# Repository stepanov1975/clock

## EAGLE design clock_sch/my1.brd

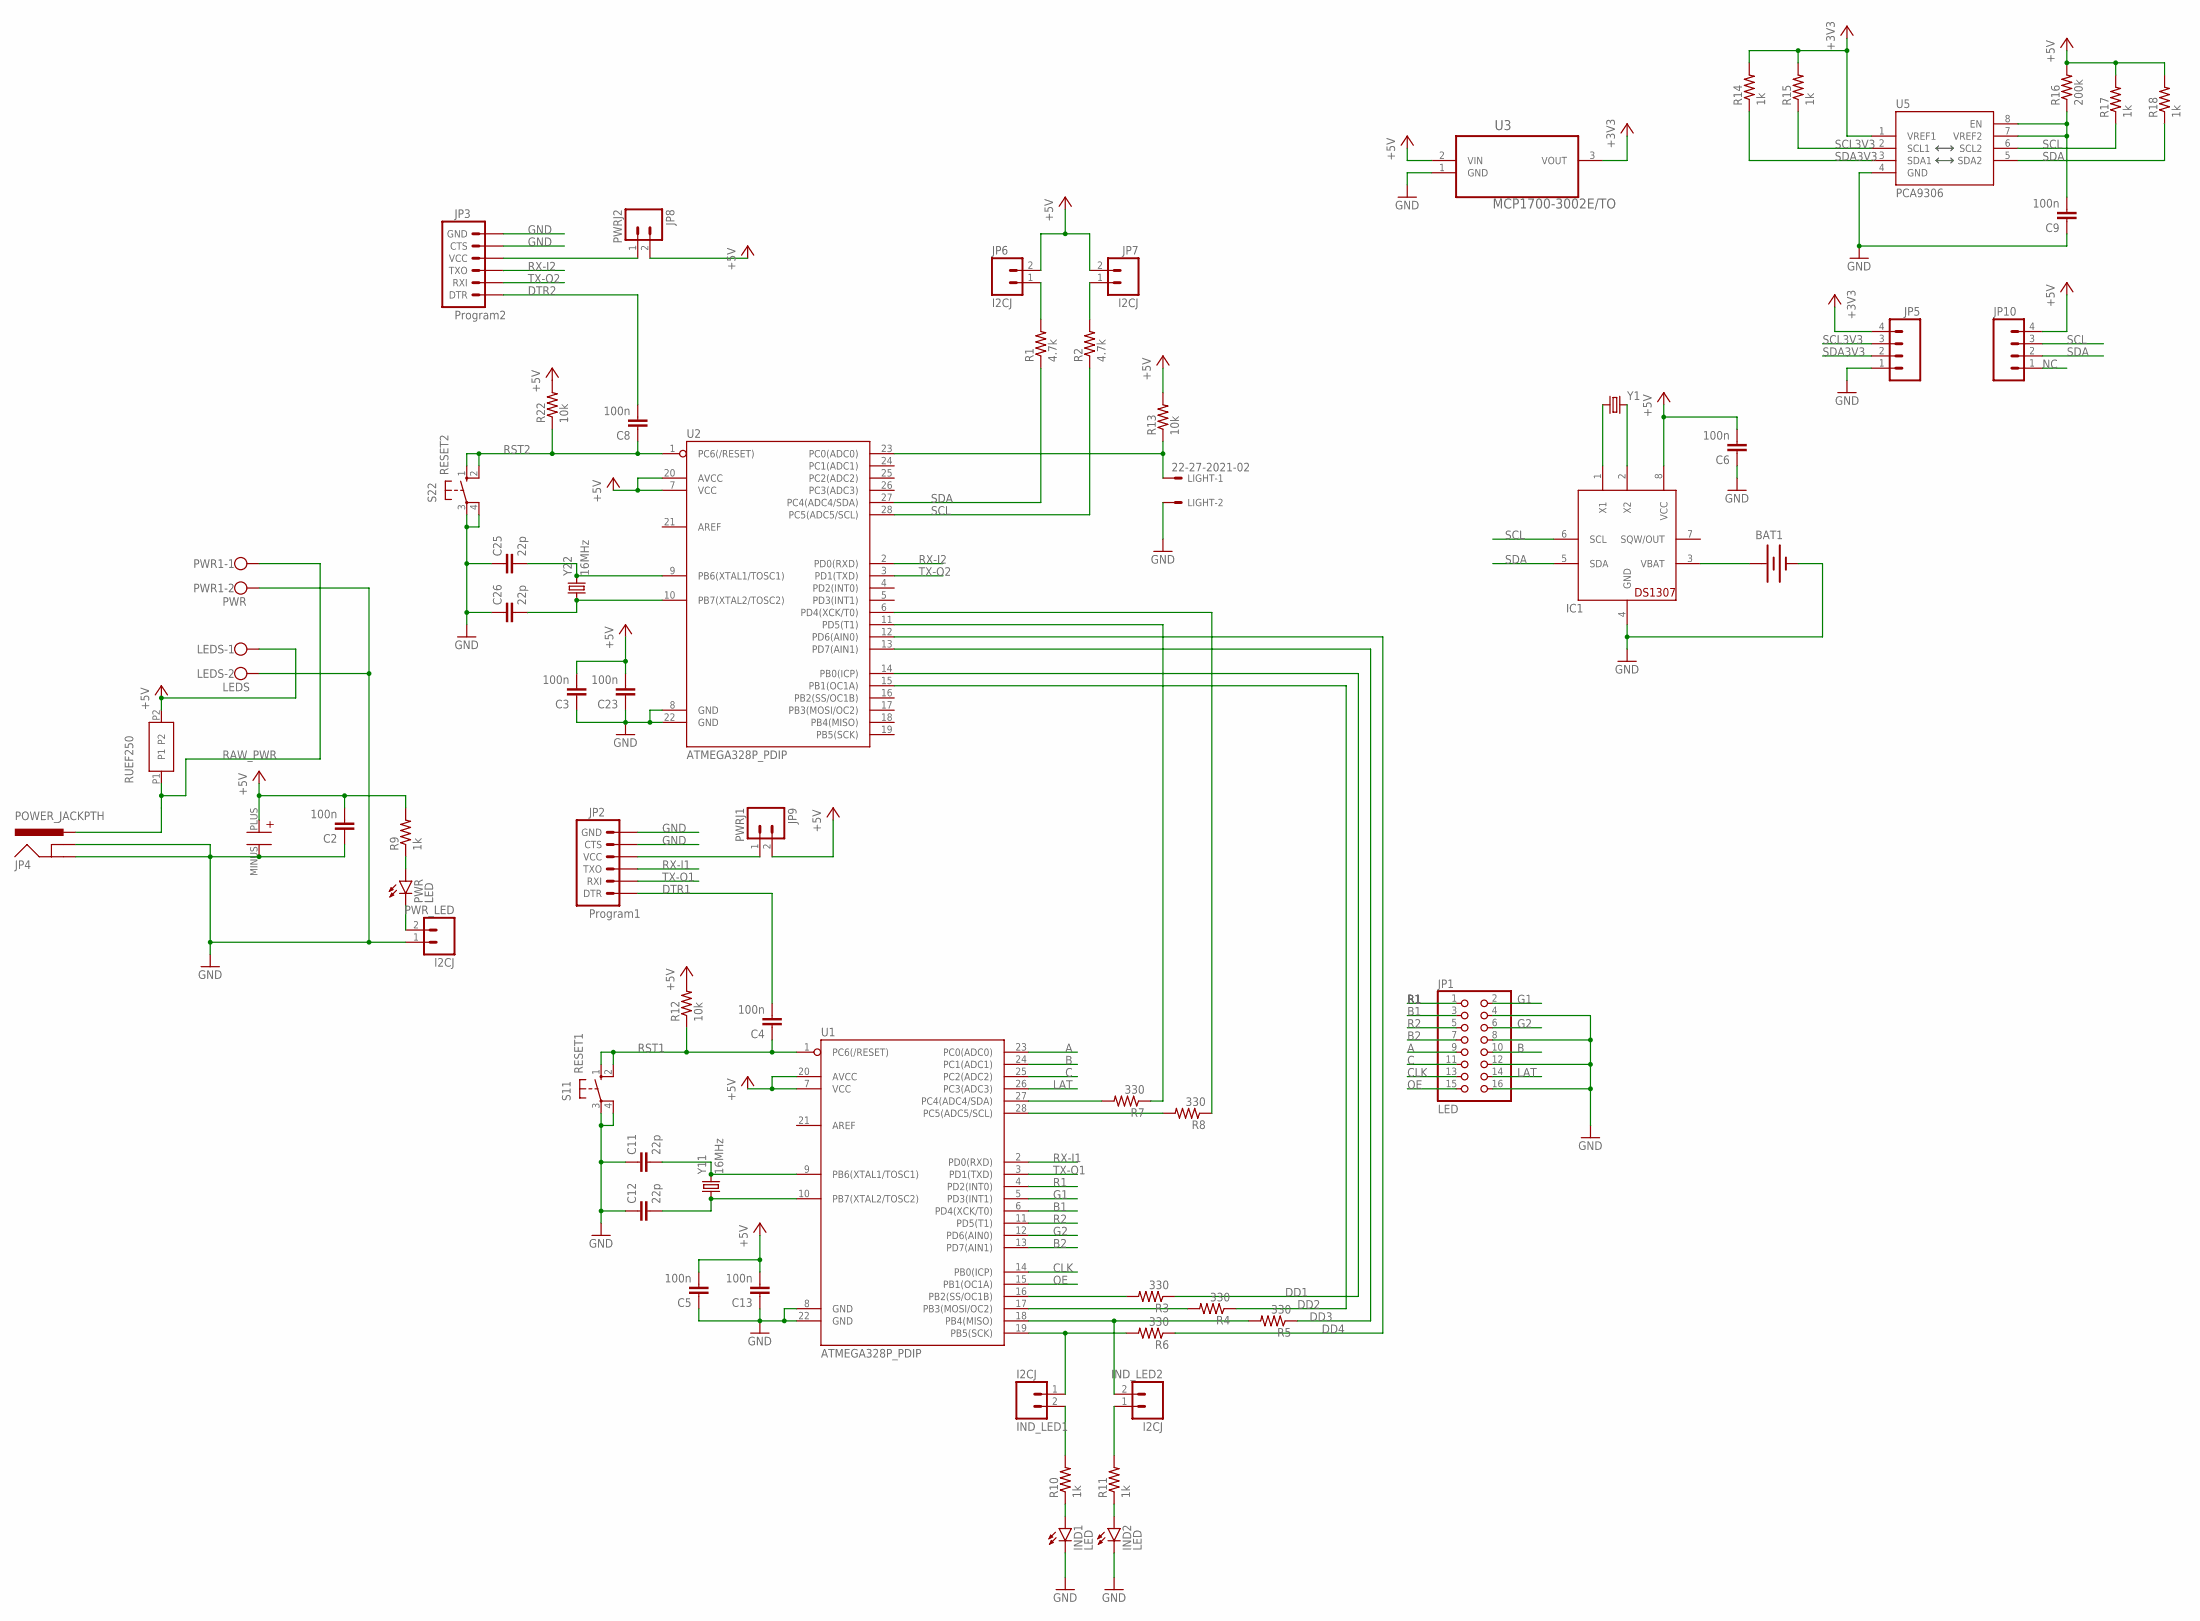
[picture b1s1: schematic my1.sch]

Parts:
BAT1: BATTERY12MM; BATTCON_12MM
C1: EEU-FR1C471B
C2, C3, C4, C5, C6, C8, C9, C13, C23: 100n; C025-024X044
C11, C12, C25, C26: 22p; C025-024X044
IC1: DS1307; DIL08
IND1, IND2: LED; LED5MM
IND_LED1, IND_LED2: I2CJ; 1X02
JP1: LED; 2X08
JP2: Program1; 1X06
JP3: Program2; 1X06
JP4: POWER_JACKPTH; POWER_JACK_PTH
JP5, JP10: M04PTH; 1X04
JP6, JP7: I2CJ; 1X02
JP8: PWRJ2; 1X02
JP9: PWRJ1; 1X02
LEDS: LEDS; W237-102
LIGHT: 22-27-2021-02; 6410-02
PWR: LED; LED5MM
PWR1: PWR; W237-102
PWR_LED: I2CJ; 1X02
R1, R2: 4.7k; AXIAL-0.3
R3, R4, R5, R6, R7, R8: 330; AXIAL-0.3
R9, R10, R11, R14, R15, R17, R18: 1k; AXIAL-0.3
R12, R13, R22: 10k; AXIAL-0.3
R16: 200k; AXIAL-0.3
RUEF250: RUEF250U
S11: RESET1; B3F-10XX
S22: RESET2; B3F-10XX
U1, U2: ATMEGA328P_PDIP; DIL28-3
U3: MCP1700-3002E/TO; TO127P254X495-3
U5: PCA9306; PSOP-8
Y1: CRYSTAL32-SMD; CRYSTAL-32KHZ-SMD
Y11, Y22: 16MHz; HC49US

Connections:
+3V3: JP5.4, R14.P$2 (2), R15.P$2 (2), U3.3 (VOUT), U5.1 (VREF1)
+5V: C1.PLUS, C2.2, C3.2, C5.2, C6.2, C13.2, C23.2, IC1.8 (VCC), JP6.2, JP7.2, JP8.2, JP9.2, JP10.4, LEDS.1, R9.P$2 (2), R12.P$2 (2), R13.P$2 (2), R16.P$2 (2), R17.P$2 (2), R18.P$2 (2), R22.P$2 (2), RUEF250.P2, U1.7 (VCC), U1.20 (AVCC), U2.7 (VCC), U2.20 (AVCC), U3.2 (VIN)
+5V1: IND_LED1.2, R10.P$2 (2)
+5V2: IND_LED2.1, R11.P$2 (2)
A: JP1.9, U1.23 (PC0(ADC0))
B: JP1.10, U1.24 (PC1(ADC1))
B1: JP1.3, U1.6 (PD4(XCK/T0))
B2: JP1.7, U1.13 (PD7(AIN1))
C: JP1.11, U1.25 (PC2(ADC2))
CLK: JP1.13, U1.14 (PB0(ICP))
DD1: R3.P$1 (1), U2.14 (PB0(ICP))
DD2: R4.P$1 (1), U2.15 (PB1(OC1A))
DD3: R5.P$1 (1), U2.13 (PD7(AIN1))
DD4: R6.P$1 (1), U2.12 (PD6(AIN0))
DTR1: C4.2, JP2.1 (DTR)
DTR2: C8.2, JP3.1 (DTR)
G1: JP1.2, U1.5 (PD3(INT1))
G2: JP1.6, U1.12 (PD6(AIN0))
GND: BAT1.GND (-), C1.MINUS, C2.1, C3.1, C5.1, C6.1, C9.1, C11.1, C12.1, C13.1, C23.1, C25.1, C26.1, IC1.4 (GND), IND1.K (C), IND2.K (C), JP1.4, JP1.8, JP1.12, JP1.16, JP2.5 (CTS), JP2.6 (GND), JP3.5 (CTS), JP3.6 (GND), JP4.GND, JP4.GNDBREAK, JP5.1, LEDS.2, LIGHT.2, PWR1.2, PWR_LED.1, S11.3, S11.4 (P1), S22.3, S22.4 (P1), U1.8 (GND), U1.22 (GND), U2.8 (GND), U2.22 (GND), U3.1 (GND), U5.4 (GND)
LAT: JP1.14, U1.26 (PC3(ADC3))
unnamed: C11.2, U1.9 (PB6(XTAL1/TOSC1)), Y11.2
unnamed: C12.2, U1.10 (PB7(XTAL2/TOSC2)), Y11.1
unnamed: C25.2, U2.9 (PB6(XTAL1/TOSC1)), Y22.2
unnamed: C26.2, U2.10 (PB7(XTAL2/TOSC2)), Y22.1
unnamed: R7.P$1 (1), U2.11 (PD5(T1))
unnamed: IND_LED1.1, R6.P$2 (2), U1.19 (PB5(SCK))
unnamed: IND_LED2.2, R5.P$2 (2), U1.18 (PB4(MISO))
unnamed: R4.P$2 (2), U1.17 (PB3(MOSI/OC2))
unnamed: R3.P$2 (2), U1.16 (PB2(SS/OC1B))
unnamed: R7.P$2 (2), U1.27 (PC4(ADC4/SDA))
unnamed: R8.P$2 (2), U1.28 (PC5(ADC5/SCL))
unnamed: R8.P$1 (1), U2.6 (PD4(XCK/T0))
unnamed: JP3.4 (VCC), JP8.1
unnamed: PWR.A, R9.P$1 (1)
unnamed: PWR.K (C), PWR_LED.2
unnamed: JP2.4 (VCC), JP9.1
unnamed: JP6.1, R1.P$2 (2)
unnamed: JP7.1, R2.P$2 (2)
unnamed: IND2.A, R11.P$1 (1)
unnamed: IND1.A, R10.P$1 (1)
unnamed: LIGHT.1, R13.P$1 (1), U2.23 (PC0(ADC0))
unnamed: C9.2, R16.P$1 (1), U5.7 (VREF2), U5.8 (EN)
unnamed: BAT1.PWR@1 (+), IC1.3 (VBAT)
unnamed: IC1.1 (X1), Y1.X1 (1)
unnamed: IC1.2 (X2), Y1.X2 (2)
NC: JP10.1
OE: JP1.15, U1.15 (PB1(OC1A))
R1: JP1.1, U1.4 (PD2(INT0))
R2: JP1.5, U1.11 (PD5(T1))
RAW_PWR: JP4.PWR, PWR1.1, RUEF250.P1
RST1: C4.1, R12.P$1 (1), S11.1 (S), S11.2 (S1), U1.1 (PC6(/RESET))
RST2: C8.1, R22.P$1 (1), S22.1 (S), S22.2 (S1), U2.1 (PC6(/RESET))
RX-I1: JP2.3 (TXO), U1.2 (PD0(RXD))
RX-I2: JP3.3 (TXO), U2.2 (PD0(RXD))
SCL: IC1.6 (SCL), JP10.3, R2.P$1 (1), R17.P$1 (1), U2.28 (PC5(ADC5/SCL)), U5.6 (SCL2)
SCL3V3: JP5.3, R15.P$1 (1), U5.2 (SCL1)
SDA: IC1.5 (SDA), JP10.2, R1.P$1 (1), R18.P$1 (1), U2.27 (PC4(ADC4/SDA)), U5.5 (SDA2)
SDA3V3: JP5.2, R14.P$1 (1), U5.3 (SDA1)
TX-O1: JP2.2 (RXI), U1.3 (PD1(TXD))
TX-O2: JP3.2 (RXI), U2.3 (PD1(TXD))

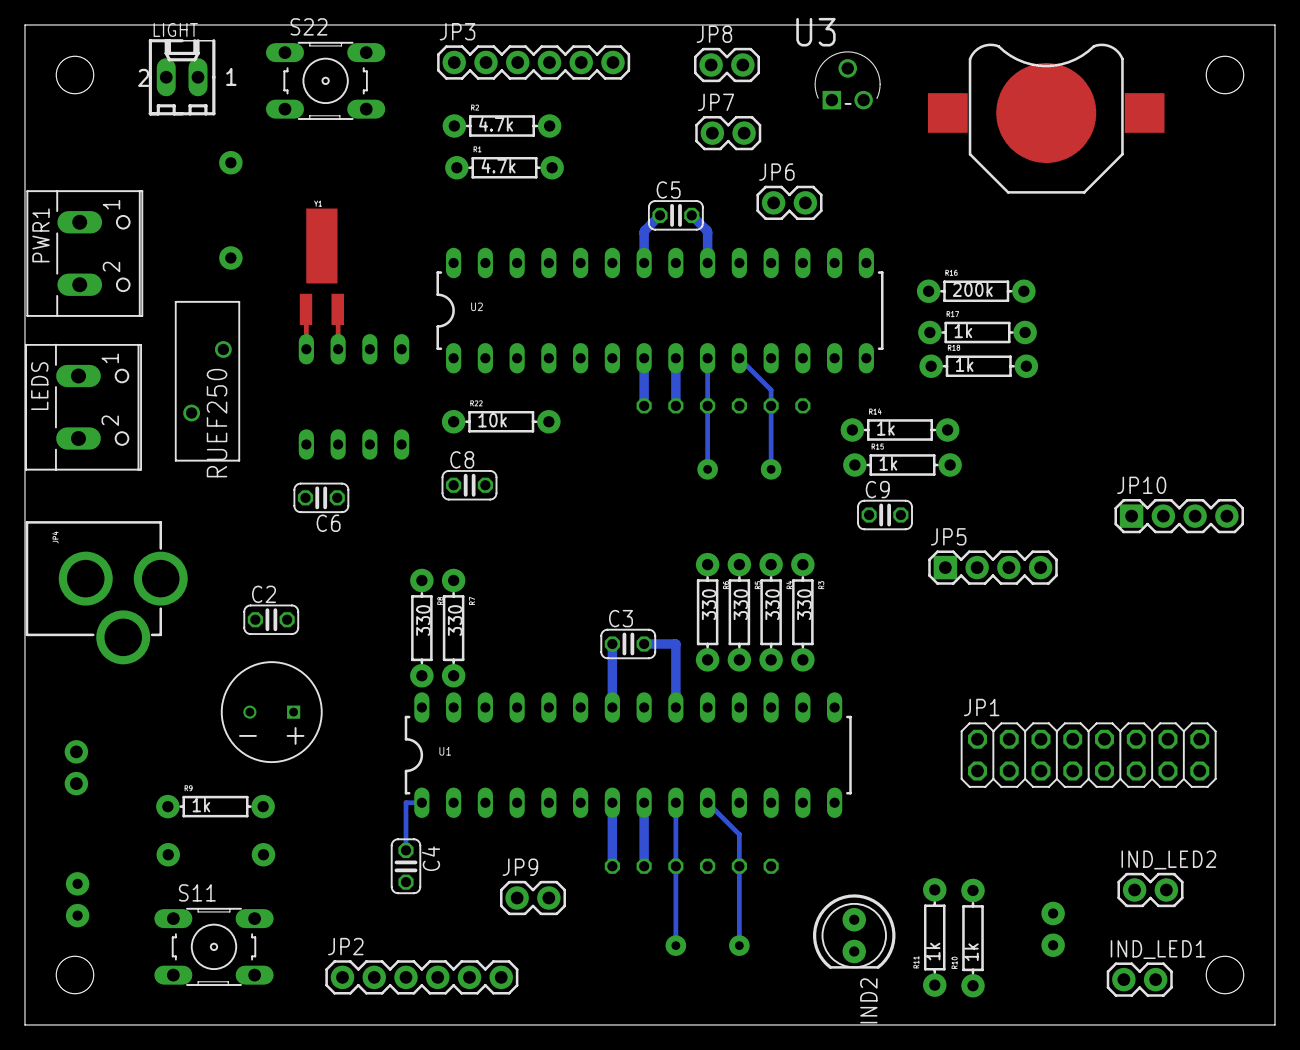
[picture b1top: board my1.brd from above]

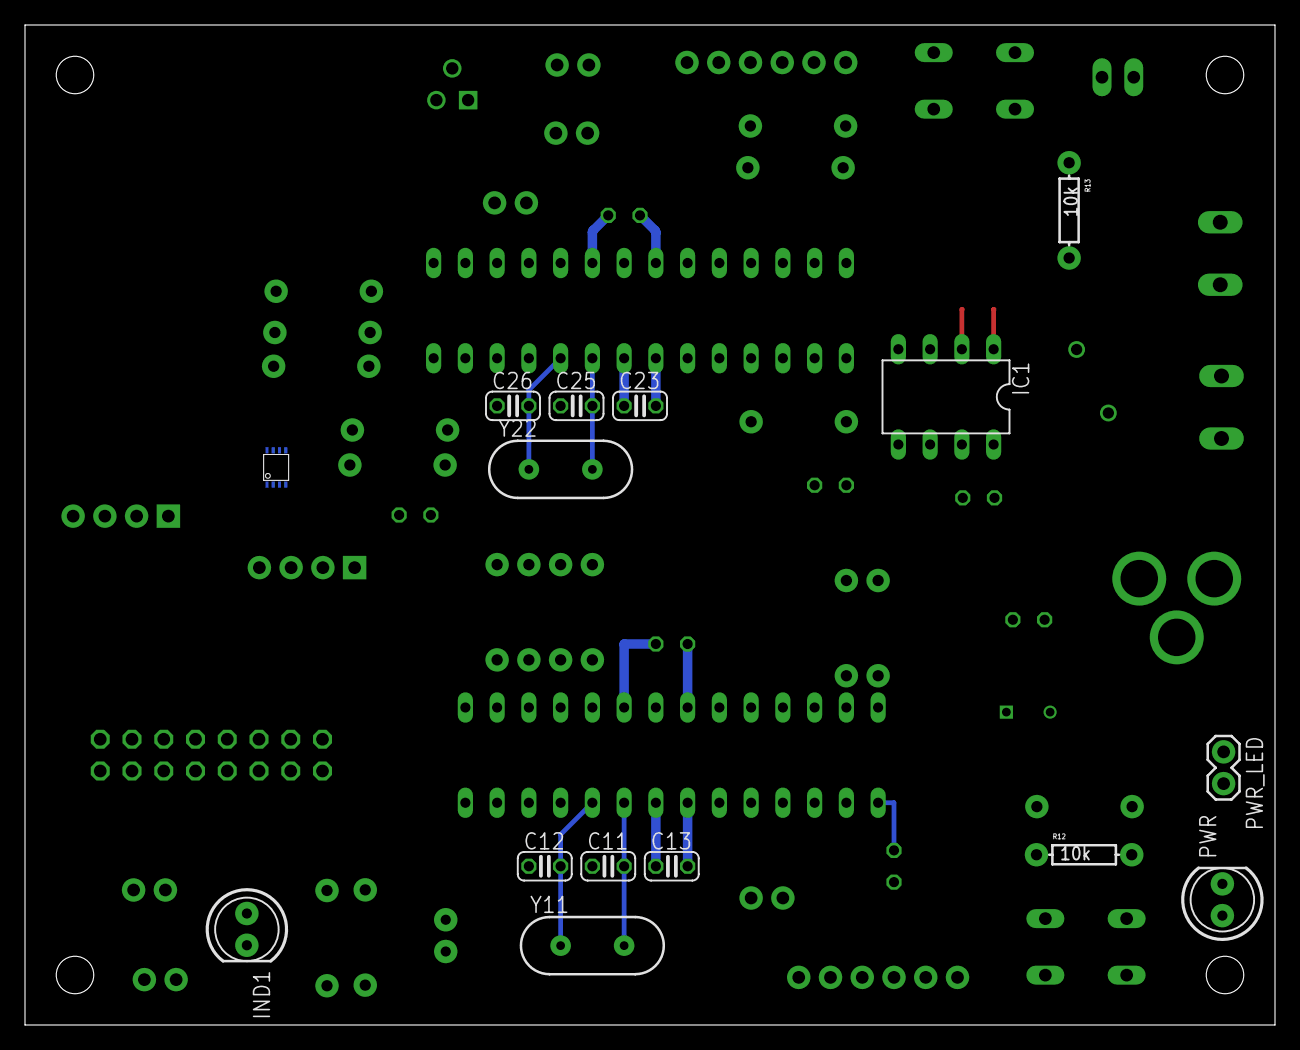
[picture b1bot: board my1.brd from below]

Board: 2 copper layers, 100.0 x 80.0 mm, 64 parts (15 on the bottom side), 59 nets.

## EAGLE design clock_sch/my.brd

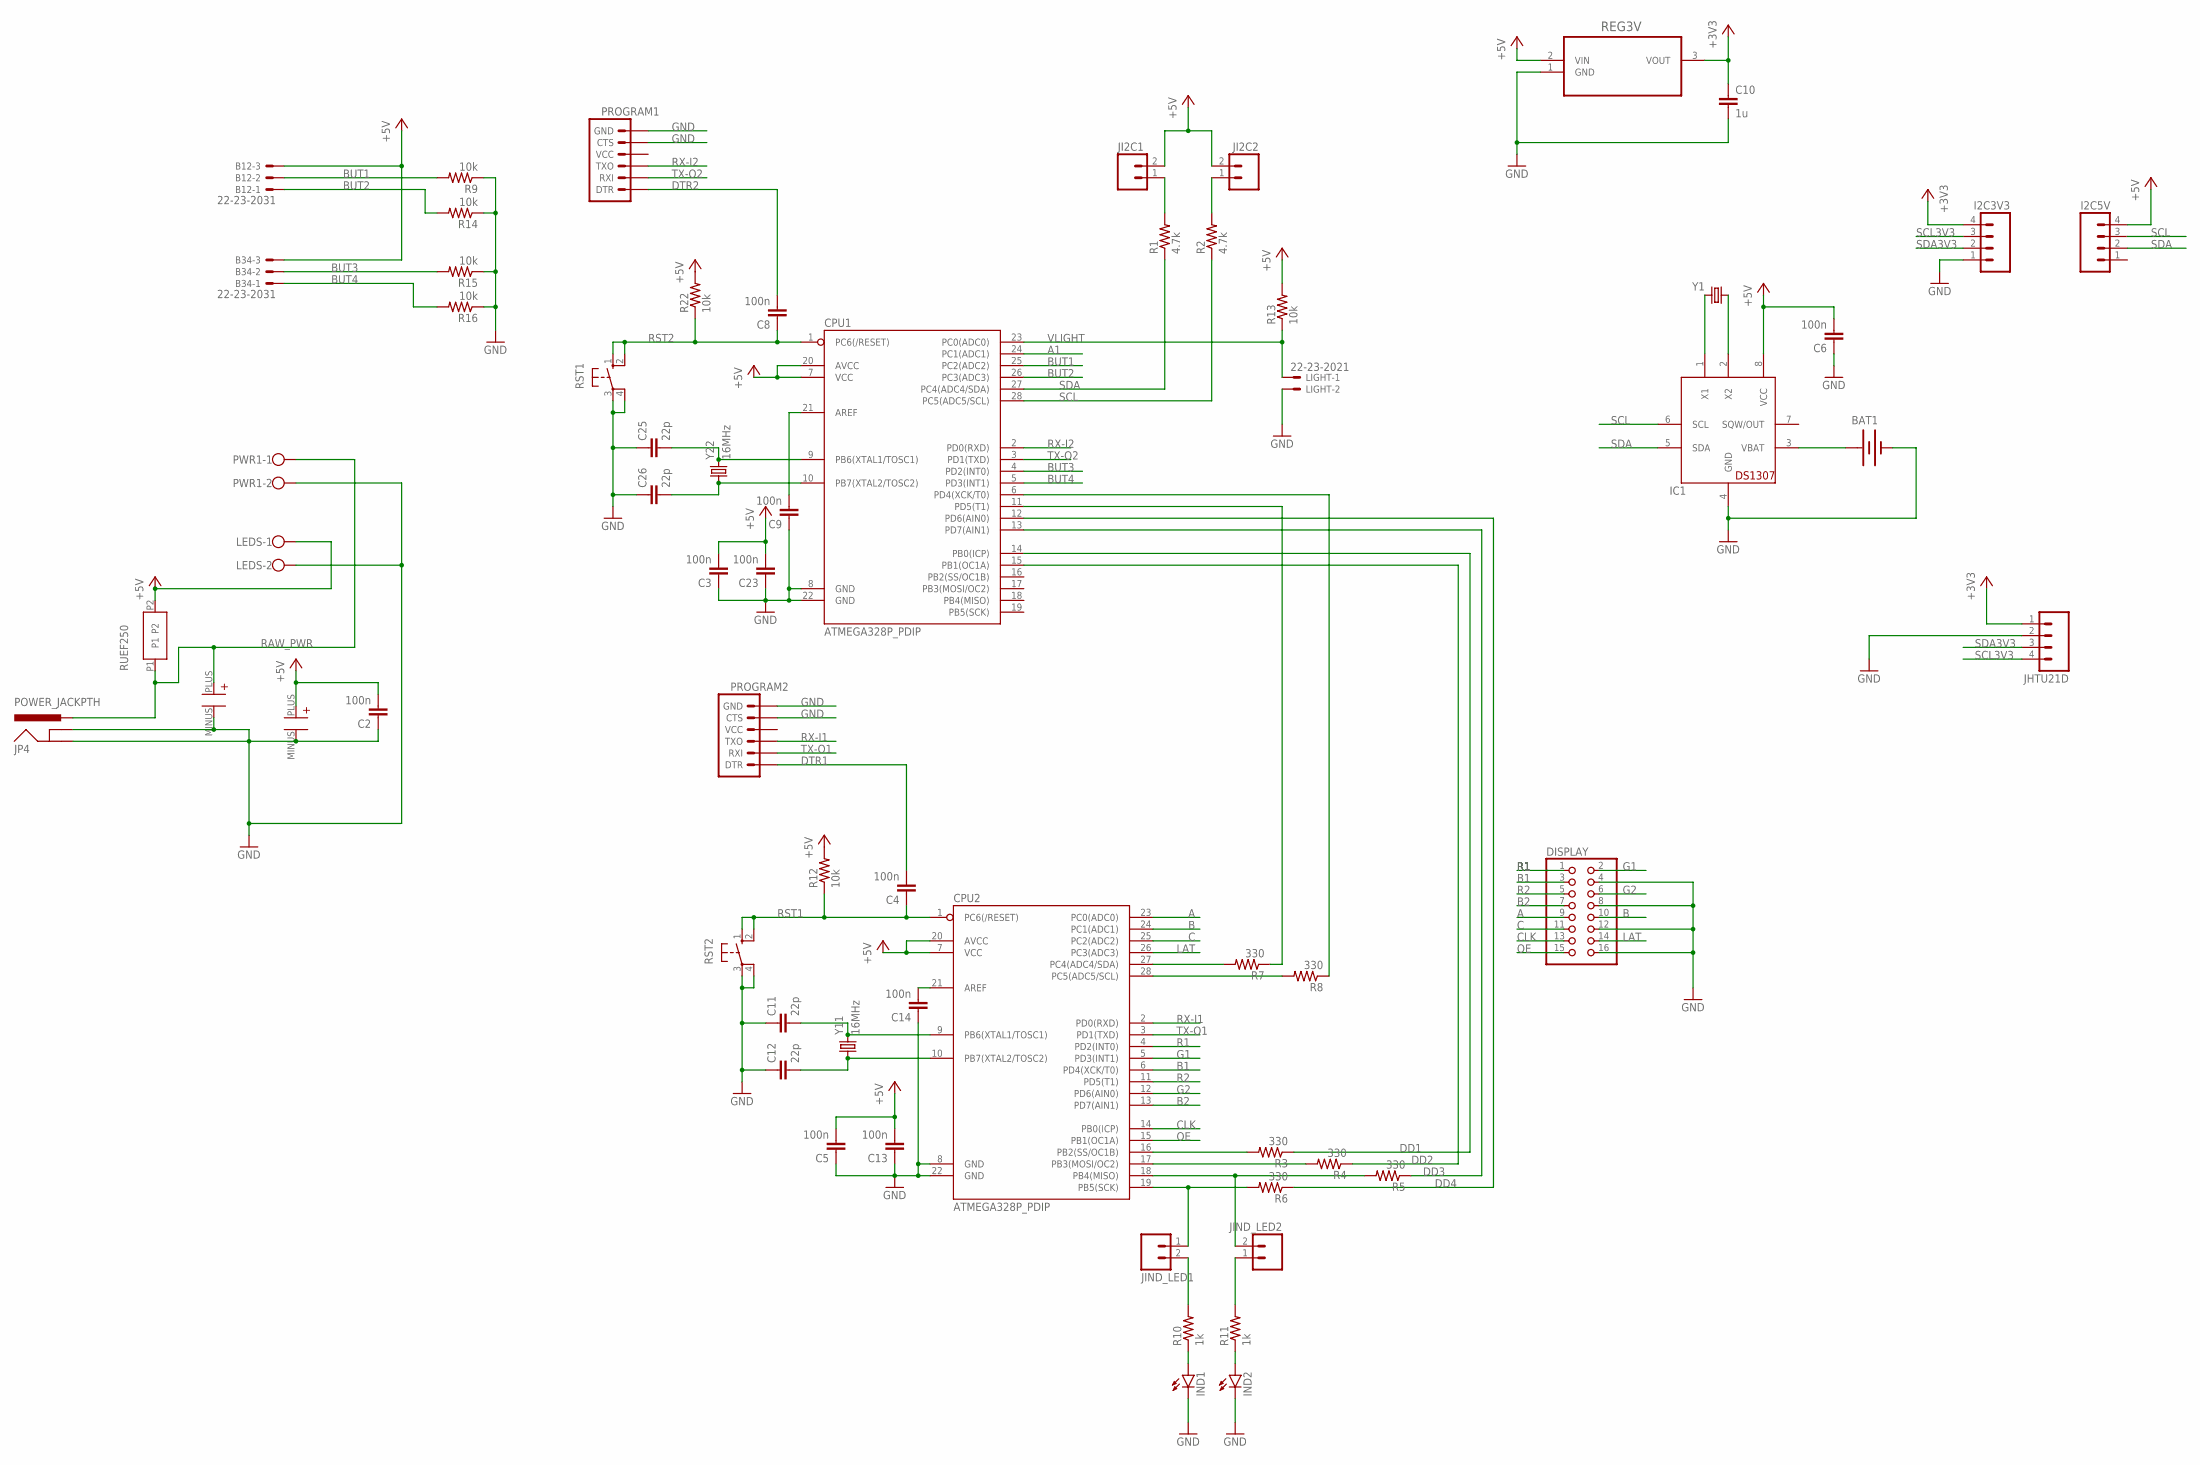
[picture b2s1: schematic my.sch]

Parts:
B12, B34: 22-23-2031
BAT1: BATTERY12MM; BATTCON_12MM
C1, C7: EEU-FR1C471B
C2, C3, C4, C5, C6, C8, C9, C13, C14, C23: 100n; C025-024X044
C10: 1u; AXIAL-5MM
C11, C12, C25, C26: 22p; C025-024X044
CPU1, CPU2: ATMEGA328P_PDIP; DIL28-3
DISPLAY: PINHD-2X8; 2X08
I2C3V3, I2C5V: M04PTH; 1X04
IC1: DS1307; DIL08
IND1, IND2: LED5MM
JHTU21D: M04PTH; 1X04
JI2C1, JI2C2: M02PTH; 1X02
JIND_LED1, JIND_LED2: M02PTH; 1X02
JP4: POWER_JACKPTH; POWER_JACK_PTH
LEDS: W237-102
LIGHT: 22-23-2021
PROGRAM1, PROGRAM2: ARDUINO_SERIAL_PROGRAMPTH; 1X06
PWR1: W237-102
R1, R2: 4.7k; AXIAL-0.3
R3, R4, R5, R6, R7, R8: 330; AXIAL-0.3
R9, R12, R13, R14, R15, R16, R22: 10k; AXIAL-0.3
R10, R11: 1k; AXIAL-0.3
REG3V: MCP1700-3002E/TO; TO127P254X495-3
RST1, RST2: 10-XX; B3F-10XX
RUEF250: RUEF250U
Y1: CRYSTAL32-SMD; CRYSTAL-32KHZ-SMD
Y11, Y22: 16MHz; HC49US

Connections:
+3V3: C10.P$1 (1), I2C3V3.4, JHTU21D.1, REG3V.3 (VOUT)
+5V: B12.3, B34.3, C1.PLUS, C2.2, C3.2, C5.2, C6.2, C13.2, C23.2, CPU1.7 (VCC), CPU1.20 (AVCC), CPU2.7 (VCC), CPU2.20 (AVCC), I2C5V.4, IC1.8 (VCC), JI2C1.2, JI2C2.2, LEDS.1, R12.P$2 (2), R13.P$2 (2), R22.P$2 (2), REG3V.2 (VIN), RUEF250.P2
+5V1: JIND_LED1.2, R10.P$2 (2)
+5V2: JIND_LED2.1, R11.P$2 (2)
A: CPU2.23 (PC0(ADC0)), DISPLAY.9
A1: CPU1.24 (PC1(ADC1))
B: CPU2.24 (PC1(ADC1)), DISPLAY.10
B1: CPU2.6 (PD4(XCK/T0)), DISPLAY.3
B2: CPU2.13 (PD7(AIN1)), DISPLAY.7
BUT1: B12.2, CPU1.25 (PC2(ADC2)), R9.P$2 (2)
BUT2: B12.1, CPU1.26 (PC3(ADC3)), R14.P$2 (2)
BUT3: B34.2, CPU1.4 (PD2(INT0)), R15.P$2 (2)
BUT4: B34.1, CPU1.5 (PD3(INT1)), R16.P$2 (2)
C: CPU2.25 (PC2(ADC2)), DISPLAY.11
CLK: CPU2.14 (PB0(ICP)), DISPLAY.13
DD1: CPU1.14 (PB0(ICP)), R3.P$1 (1)
DD2: CPU1.15 (PB1(OC1A)), R4.P$1 (1)
DD3: CPU1.13 (PD7(AIN1)), R5.P$1 (1)
DD4: CPU1.12 (PD6(AIN0)), R6.P$1 (1)
DTR1: C4.2, PROGRAM2.1 (DTR)
DTR2: C8.2, PROGRAM1.1 (DTR)
G1: CPU2.5 (PD3(INT1)), DISPLAY.2
G2: CPU2.12 (PD6(AIN0)), DISPLAY.6
GND: BAT1.GND (-), C1.MINUS, C2.1, C3.1, C5.1, C6.1, C7.MINUS, C9.1, C10.P$2 (2), C11.1, C12.1, C13.1, C14.1, C23.1, C25.1, C26.1, CPU1.8 (GND), CPU1.22 (GND), CPU2.8 (GND), CPU2.22 (GND), DISPLAY.4, DISPLAY.8, DISPLAY.12, DISPLAY.16, I2C3V3.1, IC1.4 (GND), IND1.K (C), IND2.K (C), JHTU21D.2, JP4.GND, JP4.GNDBREAK, LEDS.2, LIGHT.2, PROGRAM1.5 (CTS), PROGRAM1.6 (GND), PROGRAM2.5 (CTS), PROGRAM2.6 (GND), PWR1.2, R9.P$1 (1), R14.P$1 (1), R15.P$1 (1), R16.P$1 (1), REG3V.1 (GND), RST1.3, RST1.4 (P1), RST2.3, RST2.4 (P1)
LAT: CPU2.26 (PC3(ADC3)), DISPLAY.14
unnamed: C11.2, CPU2.9 (PB6(XTAL1/TOSC1)), Y11.2
unnamed: C12.2, CPU2.10 (PB7(XTAL2/TOSC2)), Y11.1
unnamed: C25.2, CPU1.9 (PB6(XTAL1/TOSC1)), Y22.2
unnamed: C26.2, CPU1.10 (PB7(XTAL2/TOSC2)), Y22.1
unnamed: CPU1.11 (PD5(T1)), R7.P$1 (1)
unnamed: CPU2.19 (PB5(SCK)), JIND_LED1.1, R6.P$2 (2)
unnamed: CPU2.18 (PB4(MISO)), JIND_LED2.2, R5.P$2 (2)
unnamed: CPU2.17 (PB3(MOSI/OC2)), R4.P$2 (2)
unnamed: CPU2.16 (PB2(SS/OC1B)), R3.P$2 (2)
unnamed: CPU2.27 (PC4(ADC4/SDA)), R7.P$2 (2)
unnamed: CPU2.28 (PC5(ADC5/SCL)), R8.P$2 (2)
unnamed: CPU1.6 (PD4(XCK/T0)), R8.P$1 (1)
unnamed: C9.2, CPU1.21 (AREF)
unnamed: C14.2, CPU2.21 (AREF)
unnamed: JI2C1.1, R1.P$2 (2)
unnamed: JI2C2.1, R2.P$2 (2)
unnamed: IND2.A, R11.P$1 (1)
unnamed: IND1.A, R10.P$1 (1)
unnamed: BAT1.PWR@1 (+), IC1.3 (VBAT)
unnamed: IC1.1 (X1), Y1.X2 (2)
unnamed: IC1.2 (X2), Y1.X1 (1)
OE: CPU2.15 (PB1(OC1A)), DISPLAY.15
R1: CPU2.4 (PD2(INT0)), DISPLAY.1
R2: CPU2.11 (PD5(T1)), DISPLAY.5
RAW_PWR: C7.PLUS, JP4.PWR, PWR1.1, RUEF250.P1
RST1: C4.1, CPU2.1 (PC6(/RESET)), R12.P$1 (1), RST2.1 (S), RST2.2 (S1)
RST2: C8.1, CPU1.1 (PC6(/RESET)), R22.P$1 (1), RST1.1 (S), RST1.2 (S1)
RX-I1: CPU2.2 (PD0(RXD)), PROGRAM2.3 (TXO)
RX-I2: CPU1.2 (PD0(RXD)), PROGRAM1.3 (TXO)
SCL: CPU1.28 (PC5(ADC5/SCL)), I2C5V.3, IC1.6 (SCL), R2.P$1 (1)
SCL3V3: I2C3V3.3, JHTU21D.4
SDA: CPU1.27 (PC4(ADC4/SDA)), I2C5V.2, IC1.5 (SDA), R1.P$1 (1)
SDA3V3: I2C3V3.2, JHTU21D.3
TX-O1: CPU2.3 (PD1(TXD)), PROGRAM2.2 (RXI)
TX-O2: CPU1.3 (PD1(TXD)), PROGRAM1.2 (RXI)
VLIGHT: CPU1.23 (PC0(ADC0)), LIGHT.1, R13.P$1 (1)

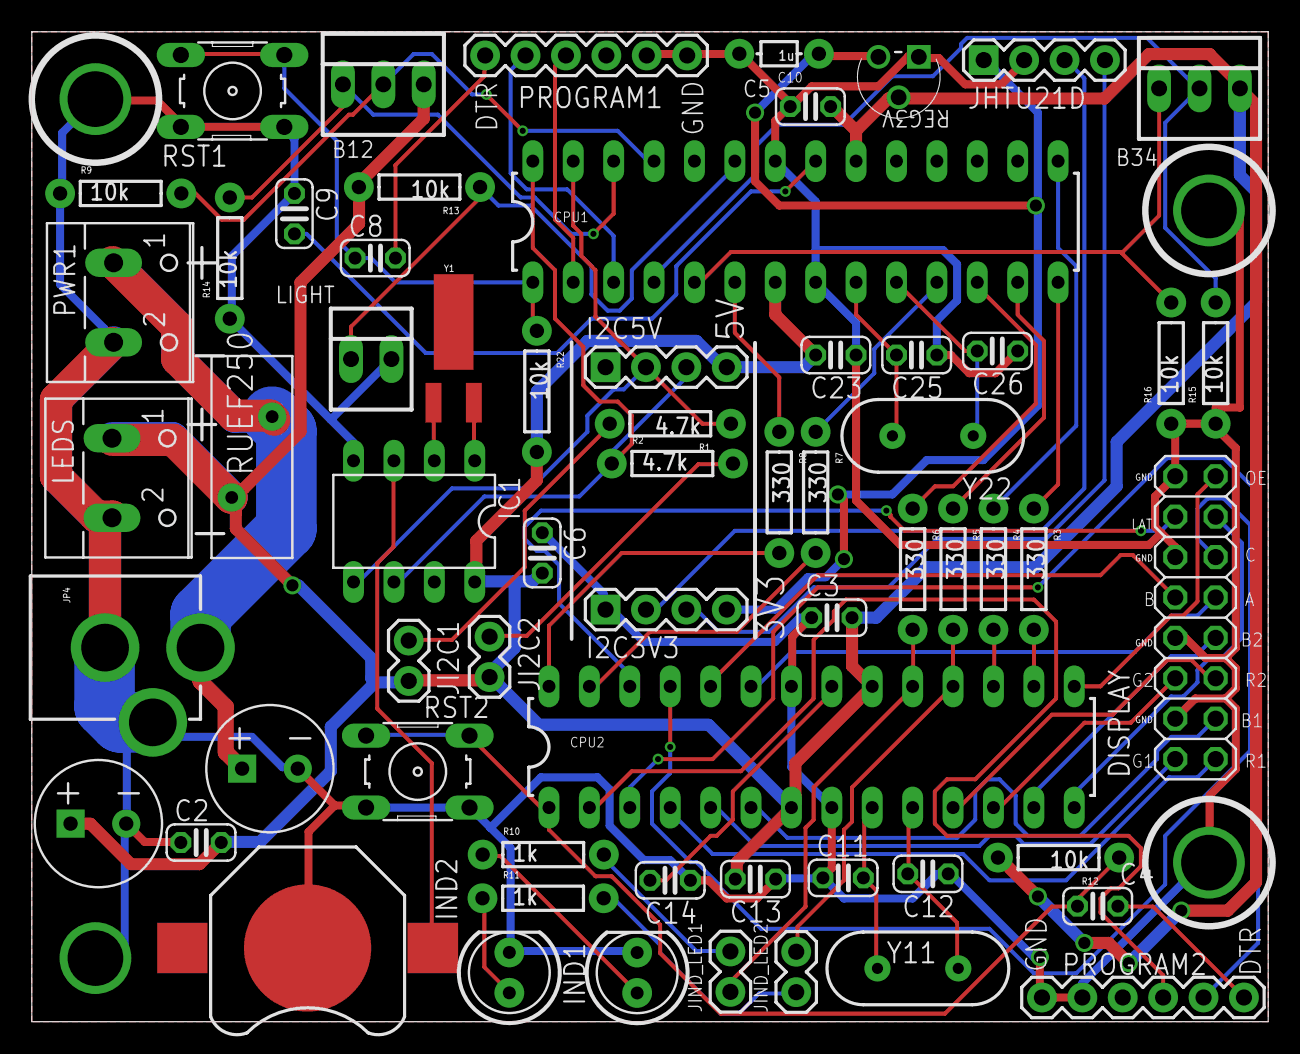
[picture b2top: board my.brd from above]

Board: 2 copper layers, 77.7 x 62.2 mm, 63 parts (0 on the bottom side), 60 nets.

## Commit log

2016-03-04 :octocat: Added .gitattributes & .gitignore files
2016-03-04 Clock

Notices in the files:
parts and their libraries:
SparkFun-Passives: Licensing: Creative Commons ShareAlike 4.0 International - https://creativecommons.org/licenses/by-sa/4.0
